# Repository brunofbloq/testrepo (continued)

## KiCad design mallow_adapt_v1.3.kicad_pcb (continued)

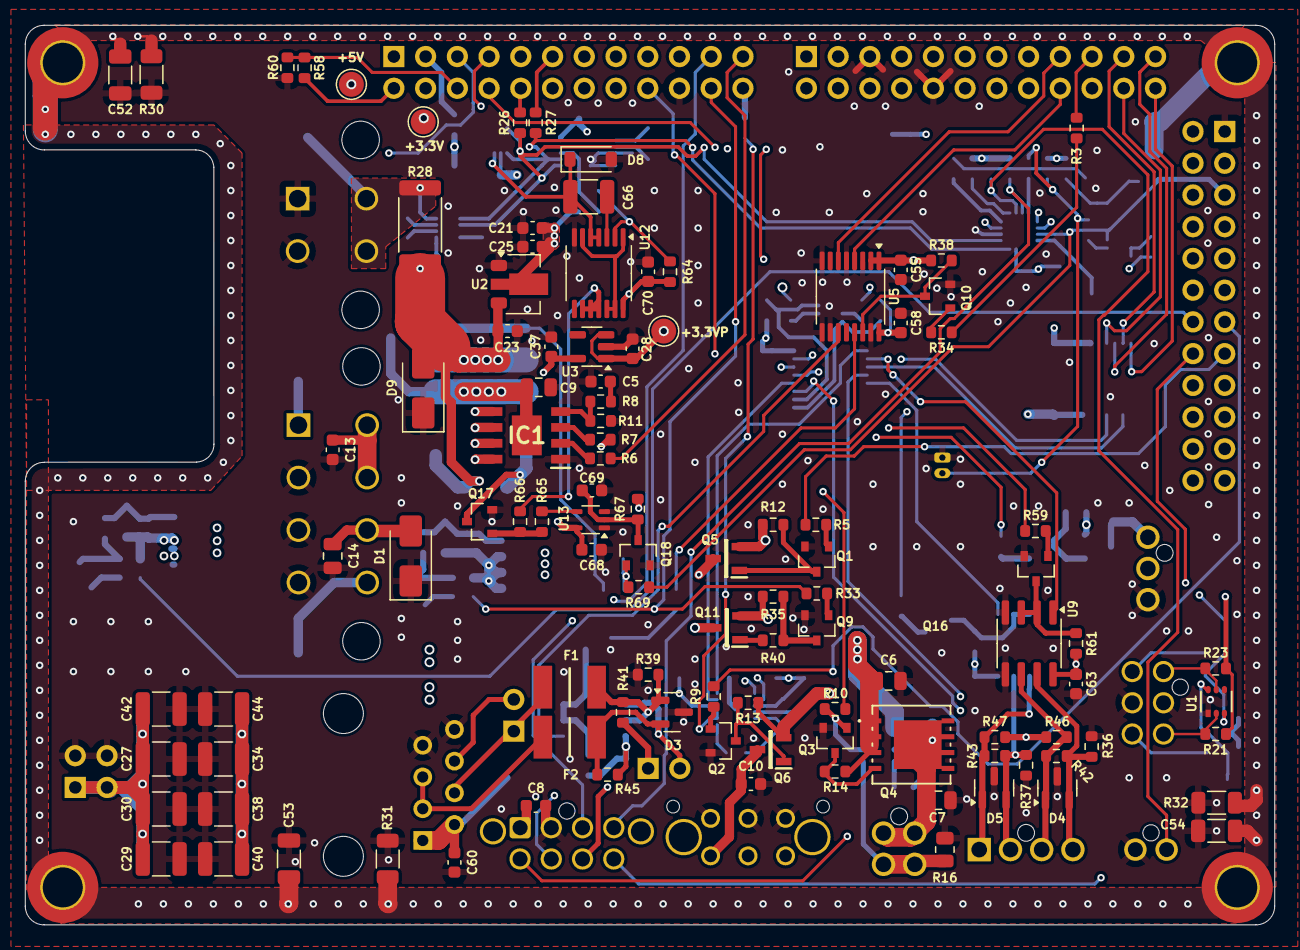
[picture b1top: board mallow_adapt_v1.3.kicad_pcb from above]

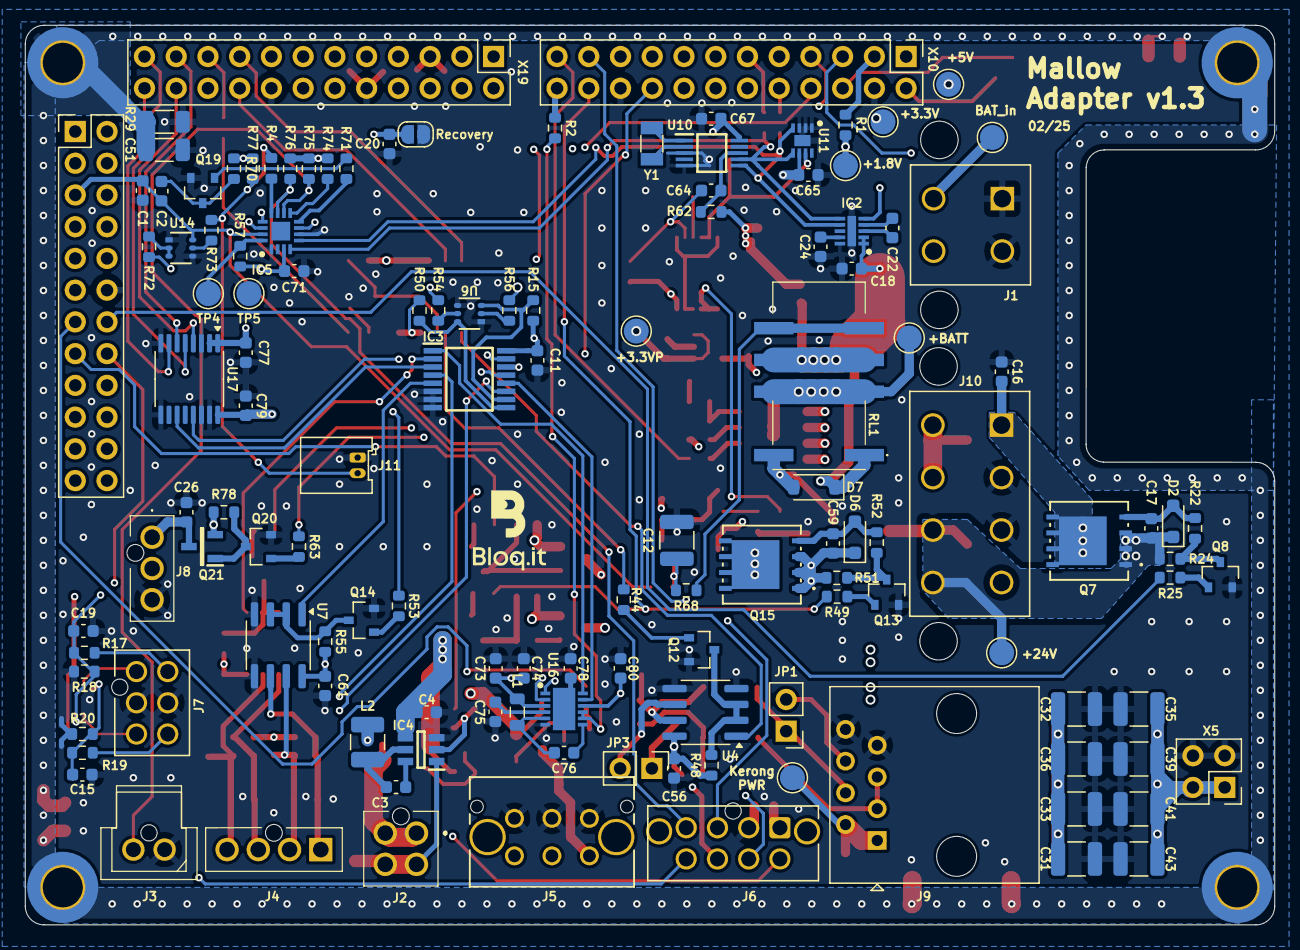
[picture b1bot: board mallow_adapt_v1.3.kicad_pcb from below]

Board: 4 copper layers, 100.0 x 72.0 mm, 240 parts (130 on the bottom side), 147 nets.

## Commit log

2025-02-27 Add files
2025-02-27 dasdre qwe
2025-02-27 Update Gpio_exp.kicad_sch
    teasstea
